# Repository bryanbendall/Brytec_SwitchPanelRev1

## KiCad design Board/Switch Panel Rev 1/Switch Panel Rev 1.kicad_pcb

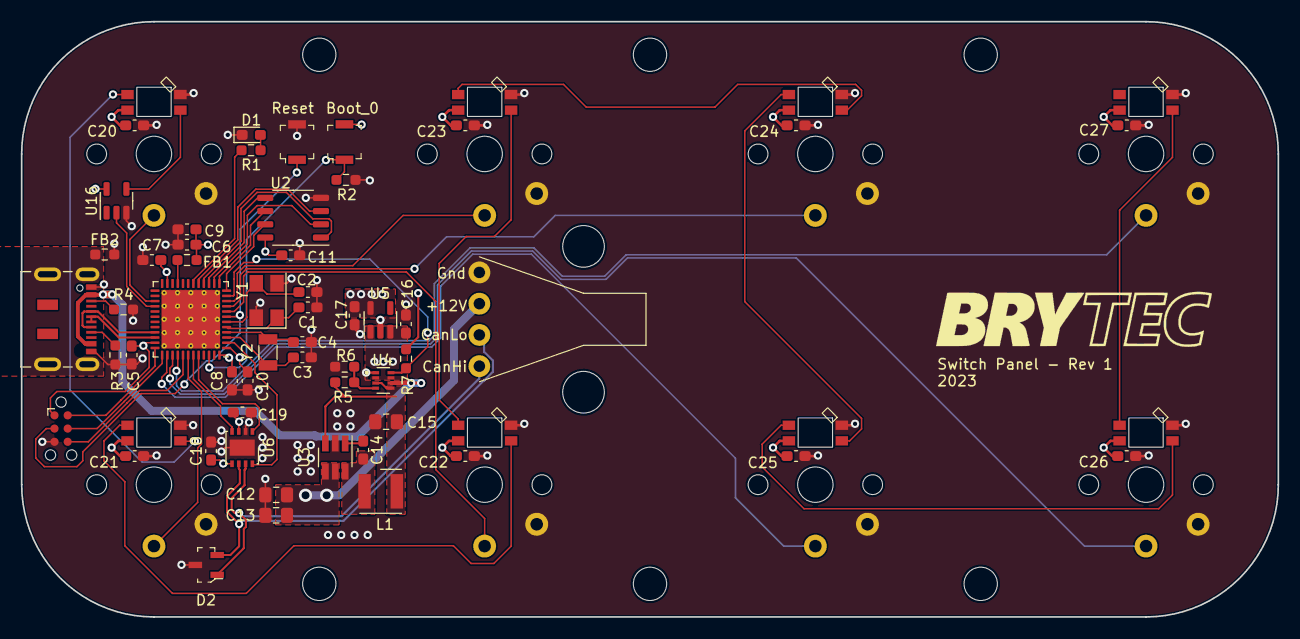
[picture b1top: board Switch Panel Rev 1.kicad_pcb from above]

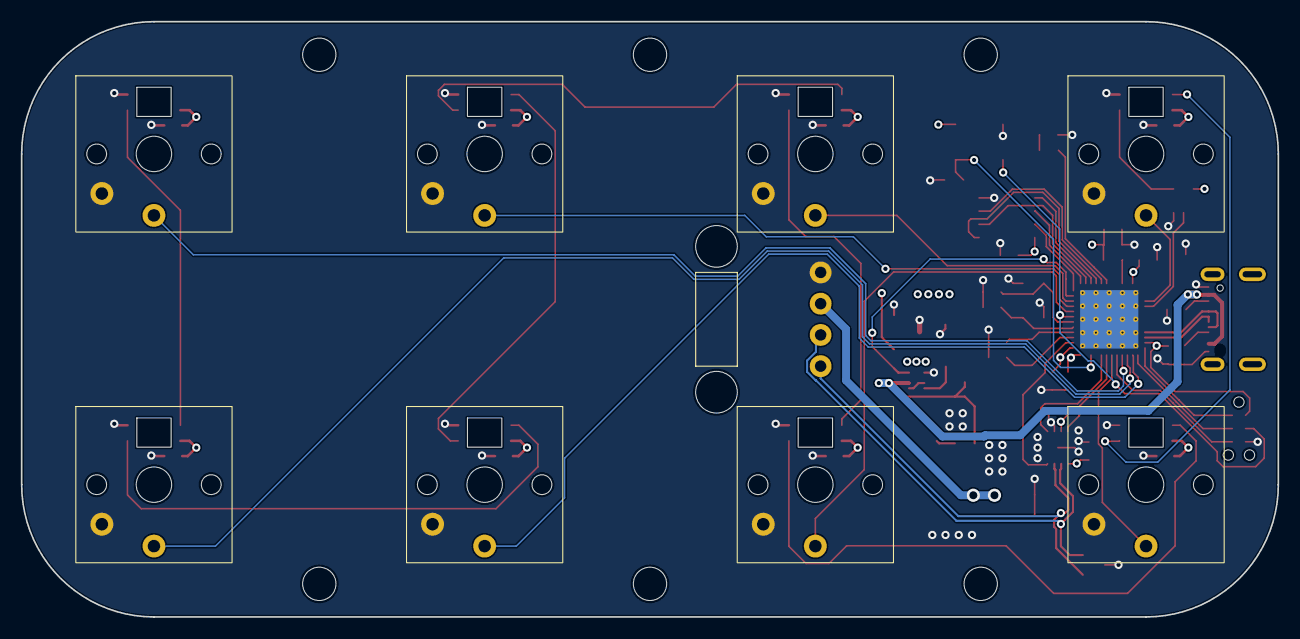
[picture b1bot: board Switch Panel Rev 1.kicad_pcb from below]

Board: 4 copper layers, 120.7 x 57.1 mm, 61 parts (8 on the bottom side), 55 nets.

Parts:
C1, C2, C3, C4: 10pF; C_0603_1608Metric_Pad1.08x0.95mm_HandSolder
C5, C7, C8, C10, C11, C14, C18, C19, C20, C21, C22, C23, C24, C25, C26, C27: 0.1uF; C_0603_1608Metric_Pad1.08x0.95mm_HandSolder
C6, C16, C17: 1uF; C_0603_1608Metric_Pad1.08x0.95mm_HandSolder
C9: 10nF; C_0603_1608Metric_Pad1.08x0.95mm_HandSolder
C12: 4.7uF; C_0805_2012Metric_Pad1.18x1.45mm_HandSolder
C13: 0.1uF; C_0805_2012Metric_Pad1.18x1.45mm_HandSolder
C15: 10uF; C_0805_2012Metric_Pad1.18x1.45mm_HandSolder
D1: LED_Small; LED_0603_1608Metric_Pad1.05x0.95mm_HandSolder
D2: PESD2CAN_215; SOT-23-3
FB1, FB2: FerriteBead_Small; R_0603_1608Metric_Pad0.98x0.95mm_HandSolder
J1: Conn_ARM_SWD_TagConnect_TC2030-NL; Tag-Connect_TC2030-IDC-NL_2x03_P1.27mm_Vertical
J2: USB_C_Receptacle_USB2.0; USB_C_Receptacle_JAE_DX07S016JA1R1500
J3: Conn_01x04; Tie Wrap Connector
L1: 6.8uH; L_Wurth_WE-LQSH-4020
R1: 65; R_0603_1608Metric_Pad0.98x0.95mm_HandSolder
R2, R5, R6, R7: 10K; R_0603_1608Metric_Pad0.98x0.95mm_HandSolder
R3, R4: 5.1K; R_0603_1608Metric_Pad0.98x0.95mm_HandSolder
S1, S2: B3U-1000P; Switch_Tactile_SMD_B3U-1000P
U1: STM32G491CEUx; QFN-48-1EP_7x7mm_P0.5mm_EP5.6x5.6mm_ThermalVias
U2: MB85RS64; SSOP-8_3.9x5.05mm_P1.27mm
U3: LMR50410Y5FQDBVRQ1; SOT-23-6_Handsoldering
U4: TPS2116DRLR; SOTFL50P160X60-8N
U5: AP2112K-3.3; SOT-23-5
U6: MCP2558FD-xMF; DFN-8-1EP_3x3mm_P0.65mm_EP1.55x2.4mm
U7, U8, U9, U10, U11, U12, U13, U14: SW_Kailh_Choc_RGB
U16: SN74LV1T34DBV; SOT-23-5
Y1: 8MHz; Crystal_SMD_5032-4Pin_5.0x3.2mm
Y2: 32.768kHz; Crystal_SMD_3215-2Pin_3.2x1.5mm

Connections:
+3.3V: C5.2, C6.2, C7.2, C8.2, C9.2, C10.2, C11.1, C17.1, C18.1, FB1.1, J1.1 (VCC), R7.1, S2.2, U1.1 (VBAT), U1.23 (VDD), U1.35 (VDD), U1.48 (VDD), U2.8 (VDD), U5.5 (VOUT), U6.5 (VIO)
+5V: C16.1, C19.1, C20.1, C21.1, C22.1, C23.1, C24.1, C25.1, C26.1, C27.1, U4.2 (VOUT), U4.7 (VOUT), U5.1 (VIN), U5.3 (EN), U6.3 (VDD), U7.1 (VDD), U8.1 (VDD), U9.1 (VDD), U10.1 (VDD), U11.1 (VDD), U12.1 (VDD), U13.1 (VDD), U14.1 (VDD), U16.5 (VCC)
/Mcu/BOOT_0: R2.1, S2.1, U1.46 (PB8)
/Mcu/Memory_Hold: U1.12 (PA4), U2.7 (~HOLD)
/Mcu/Memory_Wp: U1.17 (PB0), U2.3 (~WP)
/Mcu/RESET: J1.3 (~RESET), S1.1, U1.7 (PG10)
/Mcu/SPI1_SS_Memory: U1.16 (PC4), U2.1 (~CS)
/Mcu/SWCLK: J1.4 (SWCLK), U1.37 (PA14)
/Mcu/SWDIO: J1.2 (SWDIO), U1.36 (PA13)
/Mcu/SWO: J1.6 (SWO), U1.41 (PB3)
/Mcu/Usb D+: J2.A6 (D+), J2.B6 (D+), U1.34 (PA12)
/Mcu/Usb D-: J2.A7 (D-), J2.B7 (D-), U1.33 (PA11)
/Mcu/Usb_Shield: FB2.1, J2.S1 (SHIELD)
/Mcu/User_Led: R1.1, U1.18 (PB1)
Can+: D2.1 (C1), J3.1, U6.7 (CANH)
Can-: D2.2 (C2), J3.2, U6.6 (CANL)
CanRx: U1.43 (PB5), U6.4 (RXD)
CanSilent: U1.2 (PC13), U6.8 (S)
CanTx: U1.44 (PB6), U6.1 (TXD)
GND: C1.1, C2.1, C3.1, C4.1, C5.1, C6.1, C7.1, C8.1, C9.1, C10.1, C11.2, C12.2, C13.2, C15.2, C16.2, C17.2, C18.2, C19.2, C20.2, C21.2, C22.2, C23.2, C24.2, C25.2, C26.2, C27.2, D1.1 (K), D2.3 (C3), FB2.2, J1.5 (GND), J2.A1 (GND), J2.A12 (GND), J2.B1 (GND), J2.B12 (GND), J3.4, R2.2, R3.2, R4.2, R6.2, S1.2, U1.49 (VSS), U2.4 (GND), U3.2 (GND), U4.1 (GND), U5.2 (GND), U6.2 (VSS), U6.9 (VSS), U7.3 (GND), U7.6, U8.3 (GND), U8.6, U9.3 (GND), U9.6, U10.3 (GND), U10.6, U11.3 (GND), U11.6, U12.3 (GND), U12.6, U13.3 (GND), U13.6, U14.3 (GND), U14.6, U16.3 (GND), Y1.2, Y1.4
Ignition: C12.1, C13.1, J3.3, U3.4 (EN), U3.5 (VIN)
unnamed: D1.2 (A), R1.2
unnamed: J2.A5 (CC1), R4.1
unnamed: J2.B5 (CC2), R3.1
unnamed: C3.2, U1.3 (PC14), Y2.2
unnamed: C4.2, U1.4 (PC15), Y2.1
unnamed: C1.2, U1.5 (PF0), Y1.1
unnamed: C2.2, U1.6 (PF1), Y1.3
unnamed: FB1.2, U1.21 (VDDA)
unnamed: C14.2, U3.1 (CB)
unnamed: C14.1, L1.1, U3.6 (SW)
unnamed: R5.2, R6.1, U4.4 (PR1)
unnamed: U7.2 (DO), U9.4 (DI)
unnamed: U8.2 (DO), U10.4 (DI)
unnamed: U10.2 (DO), U12.4 (DI)
unnamed: U9.2 (DO), U11.4 (DI)
unnamed: U11.2 (DO), U13.4 (DI)
unnamed: U12.2 (DO), U14.4 (DI)
unnamed: U8.4 (DI), U13.2 (DO)
unnamed: U7.4 (DI), U16.4 (Y)
PowerSwitchStatus: R7.2, U1.11 (PA3), U4.8 (ST)
RGB_DI: U1.28 (PB15), U16.2 (A)
Regulated 5V: C15.1, L1.2, R5.1, U3.3 (FB), U4.3 (VIN1), U4.5 (MODE)
SPI1_Miso: U1.14 (PA6), U2.2 (SO)
SPI1_Mosi: U1.15 (PA7), U2.5 (SI)
SPI1_Sclk: U1.13 (PA5), U2.6 (SCK)
Sw1: U1.27 (PB14), U7.5
Sw2: U1.42 (PB4), U9.5
Sw3: U1.8 (PA0), U11.5
Sw4: U1.10 (PA2), U13.5
Sw5: U1.9 (PA1), U8.5
Sw6: U1.38 (PA15), U10.5
Sw7: U1.39 (PC10), U12.5
Sw8: U1.40 (PC11), U14.5
Usb 5V: J2.A4 (VBUS), J2.A9 (VBUS), J2.B4 (VBUS), J2.B9 (VBUS), U4.6 (VIN2)

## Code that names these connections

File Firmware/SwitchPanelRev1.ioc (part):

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Mcu.Name=STM32G491C(C-E)Ux
Mcu.Package=UFQFPN48
Mcu.UserName=STM32G491CEUx
PA0.GPIOParameters=GPIO_PuPd,GPIO_Label
PA0.GPIO_Label=Sw3
PA0.GPIO_PuPd=GPIO_PULLUP
PA0.Signal=GPIO_Input
PA1.GPIOParameters=GPIO_PuPd,GPIO_Label
PA1.GPIO_Label=Sw5
PA1.GPIO_PuPd=GPIO_PULLUP
PA1.Signal=GPIO_Input
PA11.Mode=Device
PA11.Signal=USB_DM
PA12.Mode=Device
PA12.Signal=USB_DP
PA13.Mode=Serial_Wire
PA13.Signal=SYS_JTMS-SWDIO
PA14.Mode=Serial_Wire
PA14.Signal=SYS_JTCK-SWCLK
PA15.GPIOParameters=GPIO_PuPd,GPIO_Label
PA15.GPIO_Label=Sw6
PA15.GPIO_PuPd=GPIO_PULLUP
PA15.Signal=GPIO_Input
PA2.GPIOParameters=GPIO_PuPd,GPIO_Label
PA2.GPIO_Label=Sw4
PA2.GPIO_PuPd=GPIO_PULLUP
PA2.Signal=GPIO_Input
PA3.GPIOParameters=GPIO_Label
PA3.GPIO_Label=PowerSwitchStatus
PA3.Signal=GPIO_Input
PA4.GPIOParameters=PinState,GPIO_Label
PA4.GPIO_Label=Memory_Hold
PA4.PinState=GPIO_PIN_SET
PA4.Signal=GPIO_Output
PA5.Mode=Full_Duplex_Master
PA5.Signal=SPI1_SCK
PA6.Mode=Full_Duplex_Master
PA6.Signal=SPI1_MISO
PA7.Mode=Full_Duplex_Master
PA7.Signal=SPI1_MOSI
PB0.GPIOParameters=PinState,GPIO_Label
PB0.GPIO_Label=Memory_Wp
PB0.PinState=GPIO_PIN_SET
PB0.Signal=GPIO_Output
PB1.GPIOParameters=GPIO_Label
PB1.GPIO_Label=User_Led
PB1.Signal=GPIO_Output
PB14.GPIOParameters=GPIO_PuPd,GPIO_Label
PB14.GPIO_Label=Sw1
PB14.GPIO_PuPd=GPIO_PULLUP
PB14.Signal=GPIO_Input
PB15.Mode=PWM Generation3 CH3N
PB15.Signal=TIM1_CH3N
PB4.GPIOParameters=GPIO_PuPd,GPIO_Label
PB4.GPIO_Label=Sw2
PB4.GPIO_PuPd=GPIO_PULLUP
PB4.Signal=GPIO_Input
PB5.Mode=FDCAN_Activate
PB5.Signal=FDCAN2_RX
PB6.Mode=FDCAN_Activate
PB6.Signal=FDCAN2_TX
PC10.GPIOParameters=GPIO_PuPd,GPIO_Label
PC10.GPIO_Label=Sw7
PC10.GPIO_PuPd=GPIO_PULLUP
PC10.Signal=GPIO_Input
PC11.GPIOParameters=GPIO_PuPd,GPIO_Label
PC11.GPIO_Label=Sw8
PC11.GPIO_PuPd=GPIO_PULLUP
PC11.Signal=GPIO_Input
PC13.GPIOParameters=GPIO_Label
PC13.GPIO_Label=CanSilent
PC13.Signal=GPIO_Output
PC14-OSC32_IN.Mode=LSE-External-Oscillator
PC14-OSC32_IN.Signal=RCC_OSC32_IN
PC15-OSC32_OUT.Mode=LSE-External-Oscillator
PC15-OSC32_OUT.Signal=RCC_OSC32_OUT
PC4.GPIOParameters=PinState,GPIO_Label
PC4.GPIO_Label=Memory_SS
PC4.PinState=GPIO_PIN_SET
PC4.Signal=GPIO_Output
PF0-OSC_IN.Mode=HSE-External-Oscillator
PF0-OSC_IN.Signal=RCC_OSC_IN
PF1-OSC_OUT.Mode=HSE-External-Oscillator
PF1-OSC_OUT.Signal=RCC_OSC_OUT
RCC.HSE_VALUE=8000000
RCC.SYSCLKFreq_VALUE=144000000
RCC.SYSCLKSource=RCC_SYSCLKSOURCE_PLLCLK
board=custom

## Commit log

2023-09-05 Added git ignore
2023-09-06 Board Work
2023-09-08 Added mcu config file
2023-09-11 Board Updates
2023-09-28 Added output files and bom file
2023-10-25 Initial firmware setup
2023-10-25 Added submodules and setup building
2023-10-26 Added rgb led files and test
2023-11-09 Added ibom
2023-11-10 Working leds and buttons
2023-11-10 Buttons and leds in correct order
2023-11-11 Working canbus
2023-11-14 Split up can and usb
2023-11-16 Updates for submodules
2023-11-17 Turn on can interrupt
2023-11-20 Updates for canbus from submodule
2024-01-09 Added can bus defs file Updated submodules Can working better with multiple channels Starting can with speed specified
2024-01-30 Updates for submodule changes
2024-07-19 Updates for submodules updates
2024-07-19 Added jump to bootloader
